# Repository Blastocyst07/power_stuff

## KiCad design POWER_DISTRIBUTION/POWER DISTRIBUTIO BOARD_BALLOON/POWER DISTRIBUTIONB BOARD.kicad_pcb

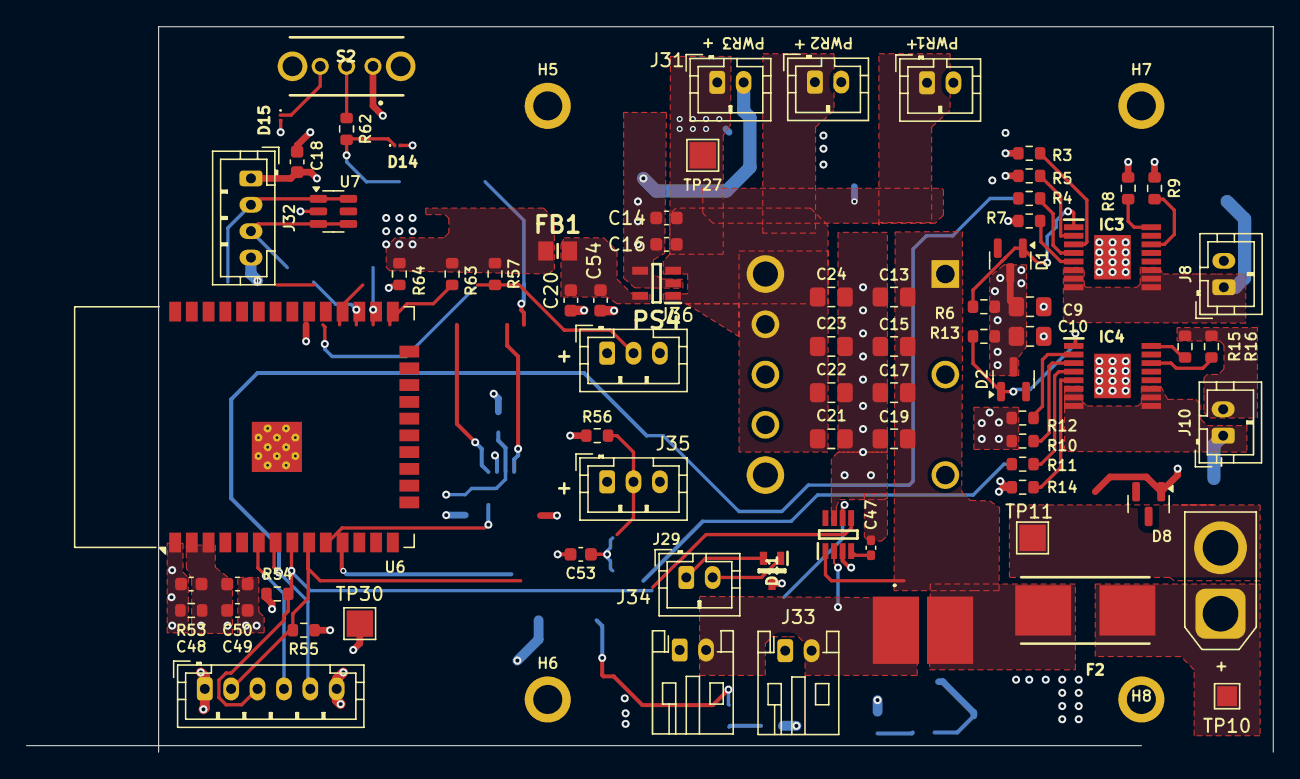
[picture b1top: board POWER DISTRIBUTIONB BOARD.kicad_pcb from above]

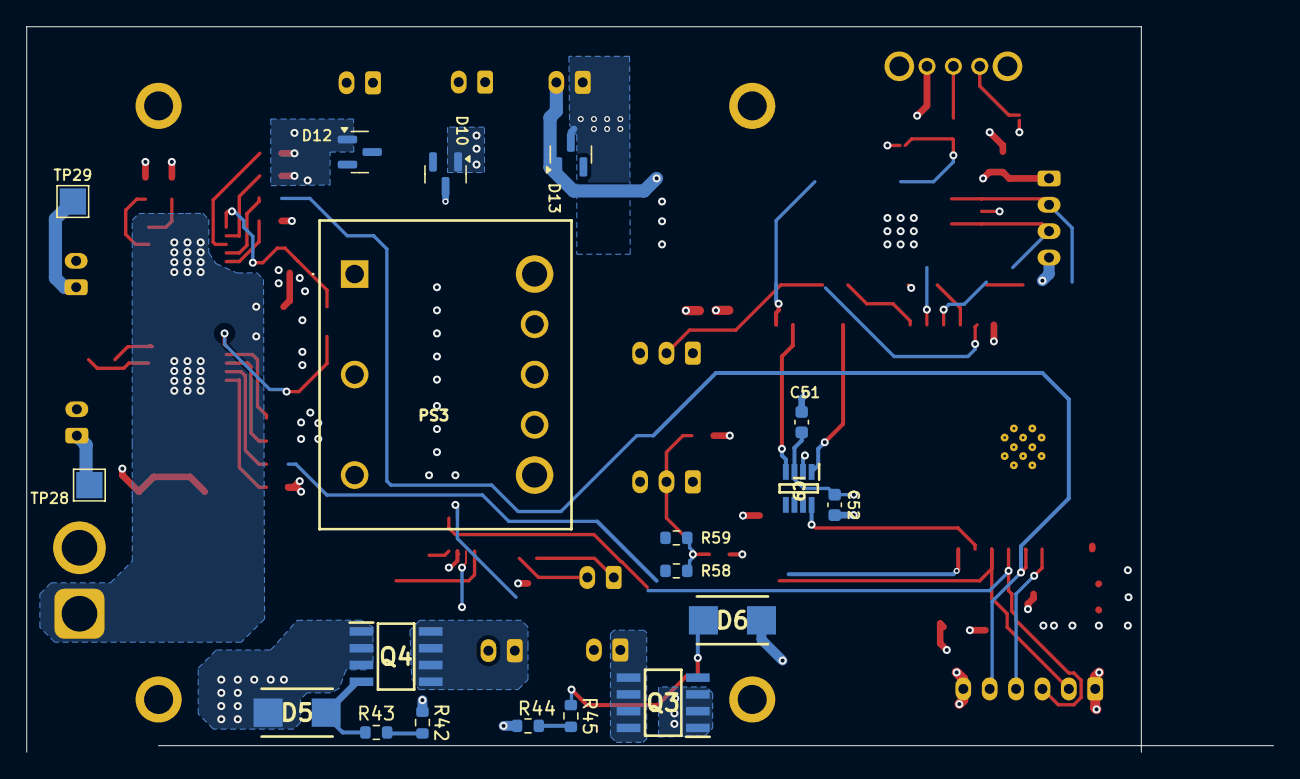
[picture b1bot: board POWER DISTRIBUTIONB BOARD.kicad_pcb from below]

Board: 4 copper layers, 94.5 x 55.0 mm, 98 parts (19 on the bottom side), 48 nets.

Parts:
C9, C10: 1uF @50V; C_0805_2012Metric_Pad1.18x1.45mm_HandSolder
C13, C15, C17, C19, C21, C22, C23, C24: 10uF@16V; C_0805_2012Metric_Pad1.18x1.45mm_HandSolder
C14, C20, C50, C52: 1uF; C_0603_1608Metric
C16, C18, C48, C49, C51, C54: 100nF; C_0603_1608Metric
C47: 100nF @50V; C_0402_1005Metric_Pad0.74x0.62mm_HandSolder
C53: 4.7nF; C_0603_1608Metric
D1, D2, D8, D10, D12, D13: BAS21; SOT-23
D5, D6: SMBJ12CA; DIONM5436X244N
D11: PESD2CANFD24V-UX; SOT65P210X110-3N
D14, D15: PESD3V3Z1BCSFYL; PMEG3005AESFYL
F2: 0154005.DRL; 0154005DRL
FB1: BLM21PG221SN1D; BEADC2012X105N
H5, H6, H7, H8: MountingHole_Pad; MountingHole_2.2mm_M2_ISO7380_Pad
IC3, IC4: TPS1HB08BQPWPRQ1; SOP65P640X120-17N
IC8: INA232AIDDFR; SOT65P280X110-8N
IC9: TCAN1044VDDFR; SOT65P280X110-8N
J8, J9, J10, J29, J30, J31: Conn_01x02; JST_PH_B2B-PH-K_1x02_P2.00mm_Vertical
J11: Conn_01x02; AMASS_XT30U-F_1x02_P5.0mm_Vertical
J28: Conn_01x06; JST_PH_B6B-PH-K_1x06_P2.00mm_Vertical
J32: Conn_01x04; JST_PH_B4B-PH-K_1x04_P2.00mm_Vertical
J33, J34: Conn_01x02; JST_PH_S2B-PH-K_1x02_P2.00mm_Horizontal
J35, J36: Conn_01x03; JST_PH_B3B-PH-K_1x03_P2.00mm_Vertical
PS3: RPMA5.0-4.5_OF; RPMA5045OF
PS4: TLV75733PDBVR; SOT95P280X145-5N
Q3, Q4: RSS070N05HZGTB; SOIC127P600X175-8N
R3, R4, R8, R9, R10, R11, R15, R16: 15k; R_0603_1608Metric
R5, R12, R62: 1K; R_0603_1608Metric
R6, R13: 4.7k; R_0603_1608Metric
R7, R14: 13.3k; R_0603_1608Metric
R42, R44: 10M; R_0603_1608Metric
R43, R45: 2k; R_0603_1608Metric
R52: WSHM28186L800FEA; WSHM2818R0330FEB
R53: 10K; R_0603_1608Metric
R54, R55, R63, R64: 2K4; R_0603_1608Metric
R56, R57: 4k7; R_0603_1608Metric
R58, R59: 60; R_0603_1608Metric
S2: OS102011MA1QN1
TP10: S2761-46R; TestPoint_Pad_1.5x1.5mm
TP11, TP27, TP28, TP29, TP30: S2761-46R; TestPoint_Pad_2.0x2.0mm
U6: ESP32-WROOM-32E; ESP32-WROOM-32D
U7: USBLC6-2SC6; SOT-23-6

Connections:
12V_BUS1: IC4.6 (VOUT_1), IC4.7 (VOUT_2), IC4.8 (VOUT_3), IC4.9 (VOUT_4), IC4.10 (VOUT_5), IC4.11 (VOUT_6), J10.1, TP28.1
12V_BUS2: IC3.6 (VOUT_1), IC3.7 (VOUT_2), IC3.8 (VOUT_3), IC3.9 (VOUT_4), IC3.10 (VOUT_5), IC3.11 (VOUT_6), J8.1, TP29.1
+3.3V: C47.2, IC8.4 (VS)
+3V3: C18.2, C48.2, C49.1, C50.1, C51.1, C52.1, D15.1 (K1), FB1.2, IC9.3 (VCC), J28.1, J32.1, J35.1, J36.1, R53.2, R54.1, R55.1, R56.1, R57.1, R63.1, R64.1, S2.3, TP30.1, U6.2 (VDD), U6.3 (EN), U7.5 (VBUS)
+5V0: C14.1, C16.1, C21.2, C22.2, C23.2, C24.2, D10.3 (K), D12.3 (K), D13.3 (K), J9.1, J30.1, J31.1, PS3.7 (+SENSE), PS3.8 (+VOUT), PS4.1 (IN), PS4.3 (EN), TP27.1
BOOT: D14.1 (K1), R62.2, U6.25 (IO0)
CAN+: D11.2 (K2), IC9.7 (CANH), J29.1, R58.2
CAN-: D11.1 (K1), IC9.6 (CANL), J29.2, R59.1
CAN_RX: IC9.4 (RXD), U6.26 (IO4)
CAN_TX: IC9.1 (TXD), U6.29 (IO5)
CUTTER_EN: J28.4, U6.6 (IO34)
GND: C9.1, C10.1, C13.1, C14.2, C15.1, C16.2, C17.1, C18.1, C19.1, C20.2, C21.1, C22.1, C23.1, C24.1, C47.1, C48.1, C49.2, C50.2, C51.2, C52.2, C53.2, C54.2, D1.3 (K), D2.3 (K), D5.1, D6.1, D8.1 (A), D10.1 (A), D11.3 (CC), D12.1 (A), D13.1 (A), D14.2 (K2), D15.2 (K2), H5.1, H6.1, H7.1, H8.1, IC8.3 (GND), IC8.7 (A0), IC9.2 (GND), IC9.8 (STB), J8.2, J9.2, J10.2, J11.2, J28.6, J30.2, J31.2, J32.4, J35.3, J36.3, PS3.3 (-VIN), PS3.4 (-VOUT), PS4.2 (GND), PS4.4 (NC), Q3.1 (SOURCE_1), Q3.2 (SOURCE_2), Q3.3 (SOURCE_3), Q4.1 (SOURCE_1), Q4.2 (SOURCE_2), Q4.3 (SOURCE_3), R3.1, R5.1, R6.2, R7.1, R8.2, R9.2, R10.1, R12.1, R13.2, R14.1, R15.2, R16.2, R42.1, R44.1, R53.1, S2.1, TP11.1, U6.1 (GND), U6.15 (GND), U6.38 (GND), U6.39 (GND), U7.2 (GND)
GPIO1_EN: R42.2, R43.2
GPIO2_EN: R44.2, R45.2
HEATER_EN: R11.1, U6.11 (IO26)
I2C2_SDA: IC8.6 (SDA), J28.3, R54.2, U6.8 (IO32)
I2C2_SDL: IC8.5 (SCL), J28.2, R55.2, U6.9 (IO33)
I2C_SDA: R63.2, U6.33 (IO21)
I2C_SDL: R64.2, U6.36 (IO22)
unnamed: C53.1, R58.1, R59.2
unnamed: D1.1 (A), IC3.1 (GND), R6.1
unnamed: D2.1 (A), IC4.1 (GND), R13.1
unnamed: IC3.16 (DIA_EN), R8.1
unnamed: IC3.4 (EN), R4.2
unnamed: IC3.5 (ILIM), R7.2
unnamed: IC3.3 (LATCH), R3.2
unnamed: IC3.14 (SEL1), R9.1
unnamed: IC3.2 (SNS), R5.2
unnamed: IC4.16 (DIA_EN), R15.1
unnamed: IC4.4 (EN), R11.2
unnamed: IC4.5 (ILIM), R14.2
unnamed: IC4.3 (LATCH), R10.2
unnamed: IC4.14 (SEL1), R16.1
unnamed: IC4.2 (SNS), R12.2
unnamed: C20.1, C54.1, FB1.1, PS4.5 (OUT)
unnamed: D6.2, Q3.4 (GATE), R45.1
unnamed: D5.2, Q4.4 (GATE), R43.1
unnamed: R62.1, S2.2
PGM_RX: J32.2, U6.35 (TXD0/IO1), U7.1 (I/O1), U7.6 (I/O1)
PGM_TX: J32.3, U6.34 (RXD0/IO3), U7.3 (I/O2), U7.4 (I/O2)
PYR_1: J33.1, Q4.5 (DRAIN_1), Q4.6 (DRAIN_2), Q4.7 (DRAIN_3), Q4.8 (DRAIN_4)
PYR_2: J34.1, Q3.5 (DRAIN_1), Q3.6 (DRAIN_2), Q3.7 (DRAIN_3), Q3.8 (DRAIN_4)
VBAT+: C9.2, C10.2, D8.3 (K), F2.1, IC3.17 (VBB), IC4.17 (VBB), J11.1, TP10.1
VBAT_Fused: C13.2, C15.2, C17.2, C19.2, F2.2, IC8.1 (IN+), PS3.1 (+VIN), R52.2
VBAT_Fused_OUT: IC8.2 (IN-), J33.2, J34.2, R52.1
VTX_EN: J28.5, R4.1, U6.7 (IO35)
onewire1: J35.2, R56.2, U6.10 (IO25)
onewire2: J36.2, R57.2, U6.37 (IO23)

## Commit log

2026-03-10 new pcb power dsitrubution board (balloon)
2026-03-11 POWER BOARD LAYOUT COMPLETE
2026-03-11 added some global labels
2026-03-12 almost finished wiring
    btw for the i2c bus idk if it was meant to be SCL instead of SDL , there is alr an SDA line but i assume so
2026-03-15 edited the pcb
2026-03-15 test
2026-03-15 pcb edits
2026-03-15 edited pcb
2026-03-16 ADD BOARD SCREENSHOT, FIX TRACE
2026-03-16 layout yweaks
2026-03-16 LAYOUT CHANGES TO
2026-03-16 edited the BAT to SSC diode
2026-03-16 merge
2026-03-16 Revert "EE"
    This reverts commit ef660a395ed7d801e632db658929d1bddf35fc5d.
2026-03-16 revert commit
2026-03-16 ee_merge final
2026-03-16 test
    repush
